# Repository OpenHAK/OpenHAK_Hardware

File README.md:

# OpenHAK Hardware
## OpenSource Health Activity Kit Hardware Files

KiCad files for the beta OpenHAK boards. 

**Check the branches tab! There is a branch for the BioHacking Village Badge at DEFCON 27 and also a OSH Park Beta Tester branch**

### WARNING: Siblees don't exist!

Hi. Here you'll find everything that you need to make yourself your very own OpenHAK! If, that is, you have any spare [Simblees](https://www.digikey.com/product-detail/en/rf-digital-corporation/RFD77101/1562-1034-ND/5723430) lying around. Should you do have some Simblees that are just taking up space, then you're in luck! Simblees are very well trained to handle reflow with a hot air gun or toaster oven many, many times. Trust me, they are tough buggers. If you *don't* have any Simblees propping open your window or shimming up your wobbly cafe table, then you're out of luck... Or are you....?

## What's going on?

**O**pen**HAK** is an **O**pen source **H**ealth **A**ctivity **K**it. Right out of the box you can wear it on your wrist (or your ankle, if you're into that kind of thing) and start tracking your steps and heart rate with a mobile app. No kidding. All of it is open-source and ready to use, modify, and share. We *were* going to call it an **O**pen **S**ource **H**ealth **I**nformation **T**racker, but we don't want to confuse people.

## Who owns the data?

Data? What data? We don't own anything. We don't keep secrets from you, or try to distract you with shiny things while we stuff your data into our AI mattress monster. No. All the data is yours. YOU can delete it or share it or analyze it or whatever it. We don't care, just don't ask us for it 'cause we don't have it. It's yours and it gets stored on your phone, or tablet, or whatever you hack the OpenHAK to spit your data into.

## What's in the box

So glad you asked. Right now, we are engaging with our beta testers and the hardware has some features that we are excitedly happy to tell you about.

* BLE
	* Yes, it's a Simblee, but it's still a pretty awesome BTLE module that can do some incredibly cool stuff. We are supporting our very own OpenHAK Arduino board variant that is based on the the original Simblee board files. We've made it easy to create the .zip packet you need to upload new code over-the-air. Every OpenHAK comes preprogrammed with Nordic's DFU library installed, so you can write your own firmware and upload it over the air from your phone to your OpenHAK.
* BMI160
	* This multi-axis MEMS monster is what we're using to count your steps, and interface with your finger tapy tap taps. We are revealing full access to it's inner guts for you to transmogrify the OpenHAK into a gesture controller so you can control your monster robot to slay your adversary's monster robot(s) with a simple gesture.
* MAX30101
	* Yes, it's a MAX integrated heart rate sensor. In the BETA version we are using the MAX3010**1** variant. If you've ever used them they are super fun to play with. **We know.** It's not easy to get heart rate off of the wrist/ankle. It's not impossible, but it's hard. That's part of the reason why we're doing this, to see how an open-source community can come together and find creative ways to solve this among many problems.
* ACCESSORIES
	* We are breaking out a handful of pins (8 for the BETA version, 10 for the BioHacking Village Badge) that are user accessible. These are useful as an Arduino compatible program interface. Also, um, maybe driving an OLED display? To, maybe, let you know when your friend is texting you ('cause it's connected to your phone...)? It could also drive an ERM (vibrator, ahem) to provide haptic feedback about stuff. The point is that since it's open-source, it's up to you. We will put up PCB design guidelines and templates so that you can create the thing you want to wear on your wrist/ankle/ahem.

## What else

The board is fit with physical features that will capture pins from an 18mm watch band. 18mm is a standard watch band size so you can accessorize with watch bands to your heart's delight!

## And
We placed the MAX30101 sensor all by itself on the (recommended) skin side of the board. We did this to facilitate enclosure design. We have a prototype case (link) that performs well under reasonable circumstances (no, we haven't mountain-biked in a wintery mix with it yet...).

If you've gotten this far then you're not even halfway down! Keep mining this repo and, don't be shy, we're only an issue away!

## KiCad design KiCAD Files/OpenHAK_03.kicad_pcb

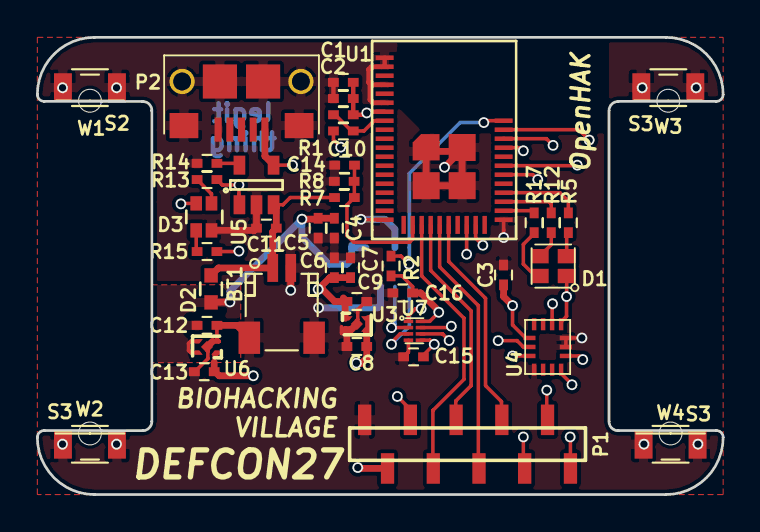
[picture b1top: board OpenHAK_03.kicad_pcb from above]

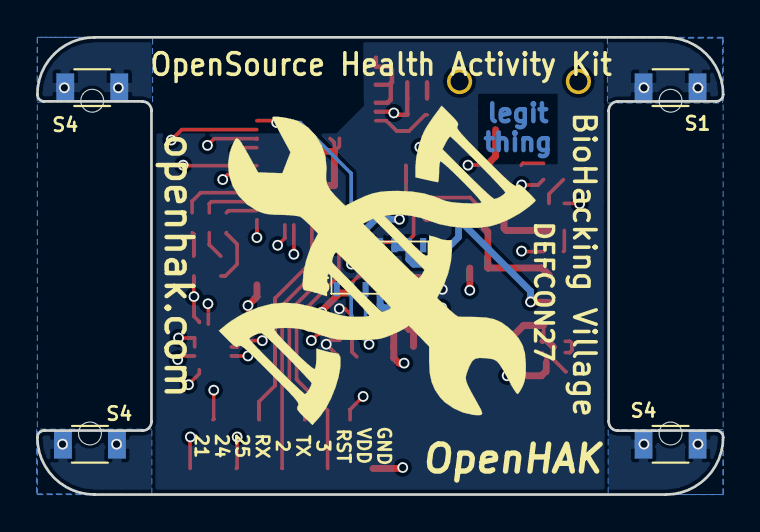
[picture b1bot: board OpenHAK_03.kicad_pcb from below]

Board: 4 copper layers, 38.1 x 25.4 mm, 51 parts (5 on the bottom side), 33 nets.

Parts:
BT1: Battery; JST_SH_SM02B-SRSS-TB_02x1.00mm_Angled
C1, C7, C10, C15, C16: 0.1uF; C_0402
C2, C4, C6, C8, C9, C12, C13, C14: 1uF; C_0402
C3, C5, C11: 10uF; C_0402
D1: ASMB-KTF0-0A306; CLMVB-FKA-CFHEHLCBB7a363
D2: D_Schottky; C_0603
D3: 18-225SURSYGC/S530-A4/E4/TR8; 0606_Bi-Color
P1: Harwin M52 Series; M52-Series_Harwin_SMT_10P
P2: USB_OTG; 10118193_microUSB
R1, R14: 10K; C_0402
R2: 4K7; C_0402
R5, R12, R17: 100R; C_0402
R7, R8: 1M; C_0402
R13, R15: 470; C_0402
S1, S2, S3, S3#2, S3#3, S4, S4#2, S4#3: C_1206
U1: rfd_77101; RFD77101
U2: MAX30100
U3: MIC5365-1.8YMT-TZ; MLF-4 1mm x 1mm
U4: BMI160; LGA_2.5x3
U5: MCP73831T-2ATI/OT; SOT-23-5
U6: MIC5365-3.0YMT-TZ; MLF-4 1mm x 1mm
U7: TXS0102DQER; X2SON8_1.4mm_x_1mm
W1, W2, W3, W4: Watch_Pin_50mil

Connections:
+1V8: C6.1, C7.2, C9.2, C15.2, U2.11, U3.1, U7.1, U7.5
/1V8_SCL: U2.2, U7.3
/1V8_SDA: U2.3, U7.2
/3V3_SCL: U1.28, U4.13, U7.6
/3V3_SDA: U1.27, U4.14, U7.7
/BMI_INT1: U1.40, U4.4
/BMI_INT2: U1.39, U4.9
/B_LED: R17.2, U1.31
/G_LED: R12.2, U1.32
/MAX_INT: R2.2, U1.41, U2.13
/PIN_2: P1.6, U1.24
/PIN_3: P1.4, U1.22
/PIN_21: P1.10, U1.36
/PIN_24: P1.9, U1.35
/PIN_25: P1.8, U1.38
/R_LED: R5.2, U1.33
/SIM_RST: C10.2, R1.2, U1.8
/SIM_RX: P1.7, U1.25
/SIM_TX: P1.5, U1.23
/V_BATT: BT1.1, C11.2, D2.2, R7.2, U5.3
/V_SENSE: C14.2, R7.1, R8.2, U1.21
GND: BT1.2, C1.1, C2.1, C3.1, C4.2, C5.2, C6.2, C7.1, C8.1, C9.1, C11.1, C12.1, C13.1, C14.1, C15.1, C16.1, D3.2, P1.1, P2.5, P2.6, P2.7, P2.8, P2.9, P2.10, P2.11, R8.1, R14.2, S1.1, S1.2, S2.1, S2.2, S3.1, S3.2, S3#2.1, S3#2.2, S3#3.1, S3#3.2, S4.1, S4.2, S4#2.1, S4#2.2, S4#3.1, S4#3.2, U1.1, U1.2, U1.4, U1.6, U1.19, U1.30, U1.42, U1.43, U1.44, U1.45, U2.4, U2.12, U3.2, U3.5, U4.1, U4.6, U4.7, U5.2, U6.2, U6.5, U7.4
unnamed: C10.1, P1.3
unnamed: D1.2, R17.1
unnamed: D1.3, R12.1
unnamed: D1.4, R5.1
unnamed: D3.1, R13.2
unnamed: D3.3, P2.1, U5.4
unnamed: D3.4, R15.2
unnamed: R13.1, R15.1, U5.1
unnamed: R14.1, U5.5
VDD: C1.2, C2.2, C3.2, C8.2, C13.2, C16.2, D1.1, P1.2, R1.1, R2.1, U1.7, U3.3, U3.4, U4.5, U4.8, U4.12, U6.1, U7.8
VPP: C4.1, C5.1, C12.2, D2.1, U2.9, U2.10, U6.3, U6.4

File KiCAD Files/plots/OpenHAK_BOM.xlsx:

Id | Designator | Package | Quantity | Designation | Manufacturer | Part Number | Distributor | Alternate Part Number | Notes
1 | BT1 | JST_SH_SM02B-SRSS-TB_02x1.00mm_Angled | 1 | Battery | JST | SM02B-SRSS-TB(LF)(SN) | TLC |  | https://www.tlcelectronics.com/tlc-3892.html
2 | C1,C7,C10,C14,C15,C16 | C_0402 | 6 | 0.1uF | Yaego | CC0402KRX5R6BB104 | Mouser
3 | C2,C4,C6,C8,C9,C12,C13 | C_0402 | 7 | 1uF | Taiyo | JMK105C6105MV-F | Mouser
4 | C3,C5,C11 | C_0402 | 3 | 10uF | Murata | GRM155R60G106ME44J | Mouser
5 | D1 | CLMVB-FKA-CFHEHLCBB7a363 | 1 | Led_RGB_CA | Broadcom | ASMB-KTF0-0A306 | Mouser | CLMVB-FKA-CFHEHLCBB7A363
6 | D2 | C_0603 | 1 | D_Schottky | Comchip | CDBU0130L | Mouser
7 | D3 | 0606_Bi-Color | 1 | Dialight_R_G_LED | Everlight | 18-225SURSYGC/S530-A4/E4/TR8 | Mouser
8 | P1 | 1x10_SMT_F | 1 | CONN_01X10 | Harwin | M52-5051045 | Newark |  | Mates with M52-040023V1045 to provide 8.5mm stack
9 | P2 | 10118193_microUSB | 1 | USB_OTG | Amphenol | 10118193-0001LF | Vertical
10 | R1,R2,R14 | C_0402 | 3 | 10K | Vishay | CRCW040210K0JNEDC | Mouser
11 | R13,R15 | C_0402 | 2 | 470R | Yaego | RC0402JR-13470RL | Mouser
12 | R5,R12,R17 | C_0402 | 3 | 100R | Yaego | RC0402FR-07100RL | Mouser
13 | R7,R8 | C_0402 | 2 | 1M | Yaego | RC0402FR-071ML | Mouser
14 | S3,S4,S4,S3,S3,S4,S1,S2 | C_1206 | 8 | Watch Pin | Vishay | CRCW12060000Z0EBC | Mouser
15 | U1 | RFD77101 | 1 | rfd_77101 | RFDigital | RFD77101 | xxx
16 | U2 | MAX3010x | 1 | MAX301_Series | Maxim | MAX30101EFD+ | Mouser
17 | U3 | MLF-4 1mm x 1mm | 1 | MIC5365 | Microchip | MIC5365-1.8YMT-TZ | Mouser
18 | U6 | MLF-4 1mm x 1mm | 1 | MIC5365 | Microchip | MIC5365-3.0YMT-TZ | Mouser
19 | U4 | LGA_2.5x3 | 1 | BMI160 | Bosch | BMI160 | Future Electronics
20 | U5 | SOT-23-5 | 1 | MCP73831 | Microchip | MCP73831T-2ATI/OT | Mouser
21 | U7 | X2SON8_1.4mm_x_1mm | 1 | TXS0102_LEVEL_SHIFTER_X2SON8 | Texas Instruments | TXS0102DQER | Texas Instruments

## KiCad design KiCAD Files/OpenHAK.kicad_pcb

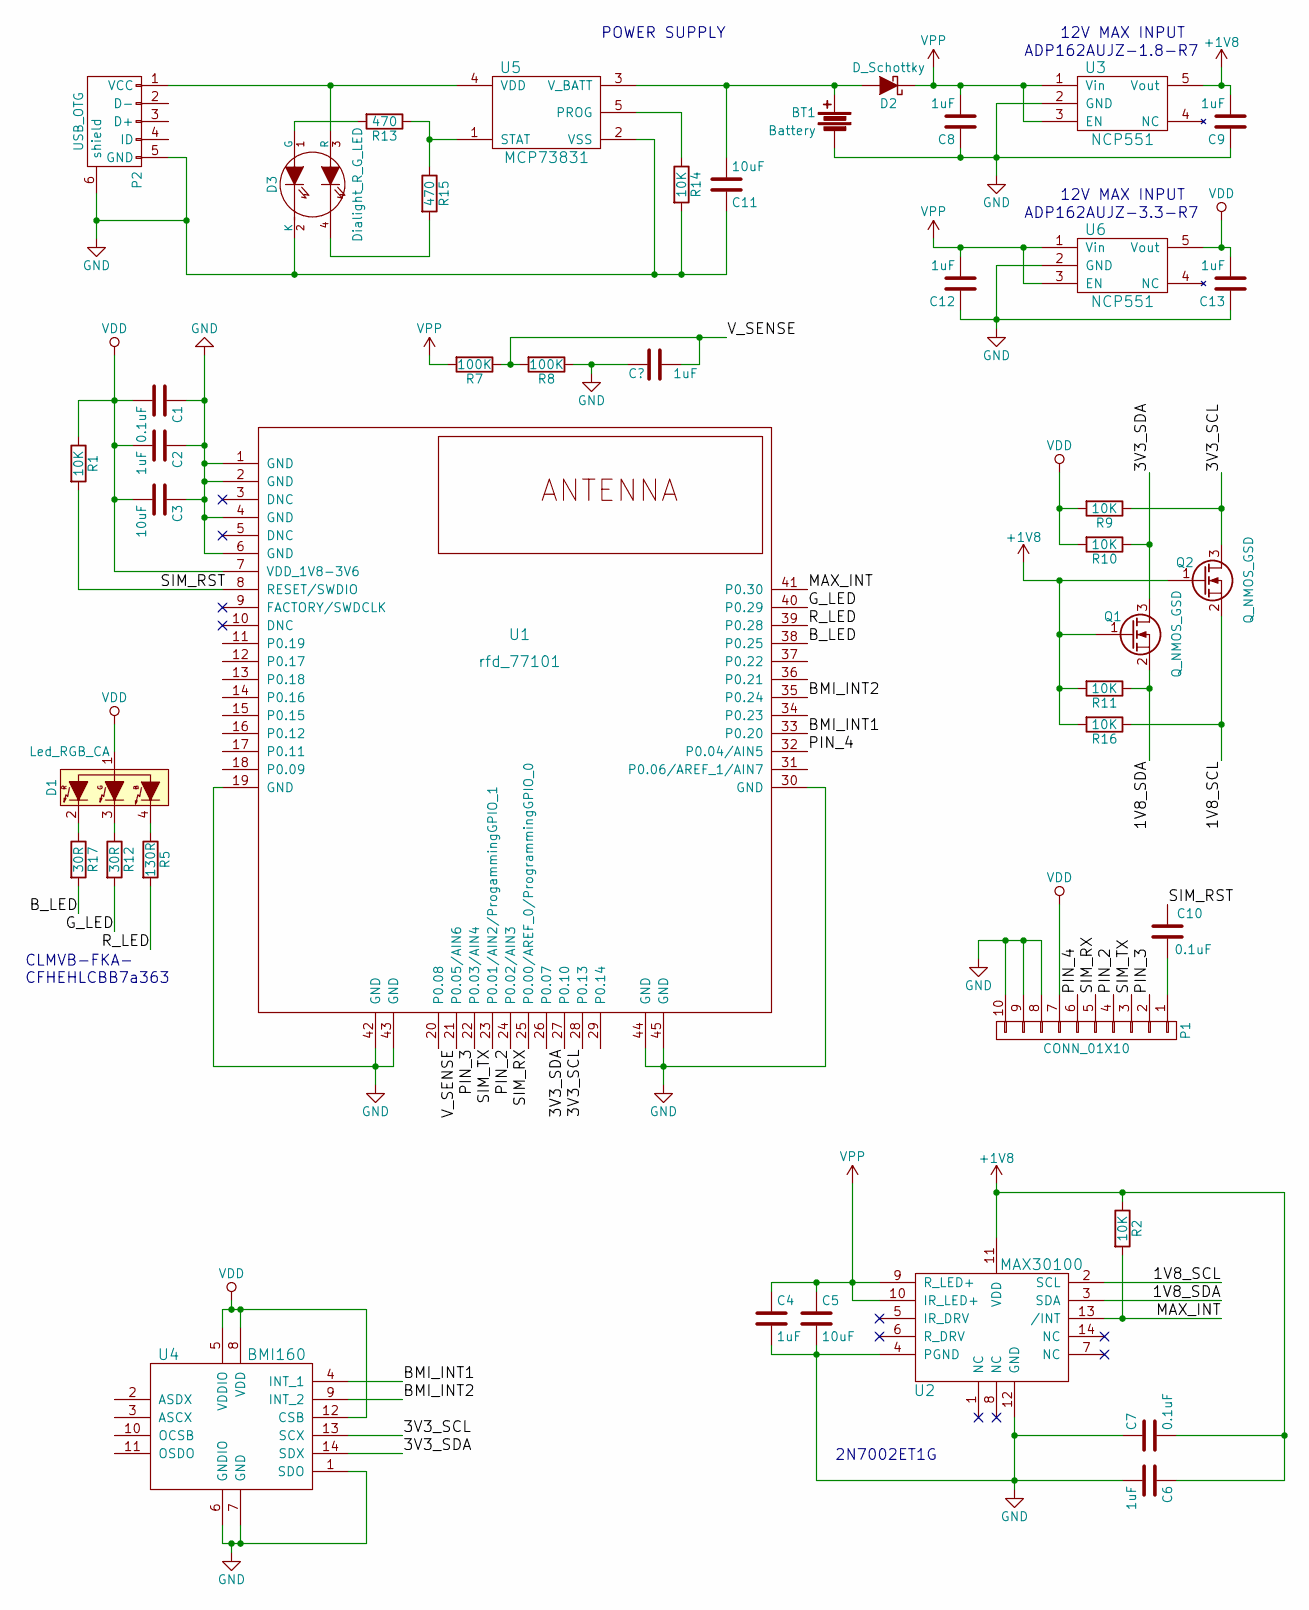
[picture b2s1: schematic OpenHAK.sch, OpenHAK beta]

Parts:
BT1: Battery; JST_RA_SMT
C1, C7, C10: 0.1uF; C_0603
C2, C4, C6, C8, C9, C12, C13: 1uF; C_0603
C3, C5, C11: 10uF; C_0603
D1: Led_RGB_CA; CLMVB-FKA-CFHEHLCBB7a363
D2: D_Schottky; C_0603
D3: Dialight_R_G_LED; 0606_Bi-Color
P1: CONN_01X10; 4u-0201GDVE06
P2: USB_OTG; 10118193_microUSB
Q1, Q2: Q_NMOS_GSD; SOT-23
R1, R2, R9, R10, R11, R14, R16: 10K; C_0603
R5: 130R; C_0603
R7, R8: 100K; C_0603
R12, R17: 30R; C_0603
R13, R15: 470; C_0603
U1: rfd_77101; RFD77101
U2: MAX30100
U3, U6: NCP551; SOT-23-5
U4: BMI160; LGA_2.5x3
U5: MCP73831; SOT-23-5

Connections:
+1V8: C6.1, C7.2, C9.2, Q1.1 (G), Q2.1 (G), R2.1, R11.2, R16.2, U2.11 (VDD), U3.5 (Vout); also elsewhere on the board
/1V8_SCL: Q2.2 (S), R16.1, U2.2 (SCL)
/1V8_SDA: Q1.2 (S), R11.1, U2.3 (SDA); also elsewhere on the board
/3V3_SCL: Q2.3 (D), R9.1, U1.28 (P0.13), U4.13 (SCX)
/3V3_SDA: Q1.3 (D), R10.1, U1.27 (P0.10), U4.14 (SDX); also elsewhere on the board
/BMI_INT1: U1.33 (P0.20), U4.4 (INT_1)
/BMI_INT2: U1.35 (P0.24), U4.9 (INT_2)
/B_LED: R17.2, U1.38 (P0.25)
/G_LED: R12.2, U1.40 (P0.29)
/MAX_INT: R2.2, U1.41 (P0.30), U2.13 (/INT)
/PIN_2: P1.4, U1.24 (P0.02/AIN3)
/PIN_3: P1.2, U1.22 (P0.03/AIN4)
/PIN_4: P1.6, U1.32 (P0.04/AIN5)
/R_LED: R5.2, U1.39 (P0.28)
/SIM_RST: C10.1, R1.2, U1.8 (RESET/SWDIO)
/SIM_RX: P1.5, U1.25 (P0.00/AREF_0/ProgrammingGPIO_0)
/SIM_TX: P1.3, U1.23 (P0.01/AIN2/ProgammingGPIO_1)
/V_SENSE: R7.1, R8.2, U1.21 (P0.05/AIN6)
GND: BT1.2, BT1.3, BT1.4, C1.1, C2.1, C3.1, C4.2, C5.2, C6.2, C7.1, C8.1, C9.1, C11.1, C12.1, C13.1, D3.2 (K), P1.8, P1.9, P1.10, P2.5 (GND), P2.6 (shield), P2.7, P2.8, P2.9, P2.10, P2.11, R8.1, R14.2, U1.1 (GND), U1.2 (GND), U1.4 (GND), U1.6 (GND), U1.19 (GND), U1.30 (GND), U1.42 (GND), U1.43 (GND), U1.44 (GND), U1.45 (GND), U2.4 (PGND), U2.12 (GND), U3.2 (GND), U4.1 (SDO), U4.6 (GNDIO), U4.7 (GND), U5.2 (VSS), U6.2 (GND)
unnamed: BT1.1, C11.2, D2.2 (A), U5.3 (V_BATT)
unnamed: C10.2, P1.1
unnamed: D1.2 (R), R17.1
unnamed: D1.3 (G), R12.1
unnamed: D1.4 (B), R5.1
unnamed: D3.1 (G), R13.2
unnamed: D3.3 (R), P2.1 (VCC), U5.4 (VDD)
unnamed: D3.4, R15.2
unnamed: R13.1, R15.1, U5.1 (STAT)
unnamed: R14.1, U5.5 (PROG)
VDD: C1.2, C2.2, C3.2, C13.2, D1.1, P1.7, R1.1, R9.2, R10.2, U1.7 (VDD_1V8-3V6), U4.5 (VDDIO), U4.8 (VDD), U4.12 (CSB), U6.5 (Vout)
VPP: C4.1, C5.1, C8.2, C12.2, D2.1 (K), R7.2, U2.9 (R_LED+), U2.10 (IR_LED+), U3.1 (Vin), U3.3 (EN), U6.1 (Vin), U6.3 (EN)

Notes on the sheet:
ADP162AUJZ-1.8-R7
POWER SUPPLY
12V MAX INPUT
2N7002ET1G
ADP162AUJZ-3.3-R7
CLMVB-FKA- CFHEHLCBB7a363

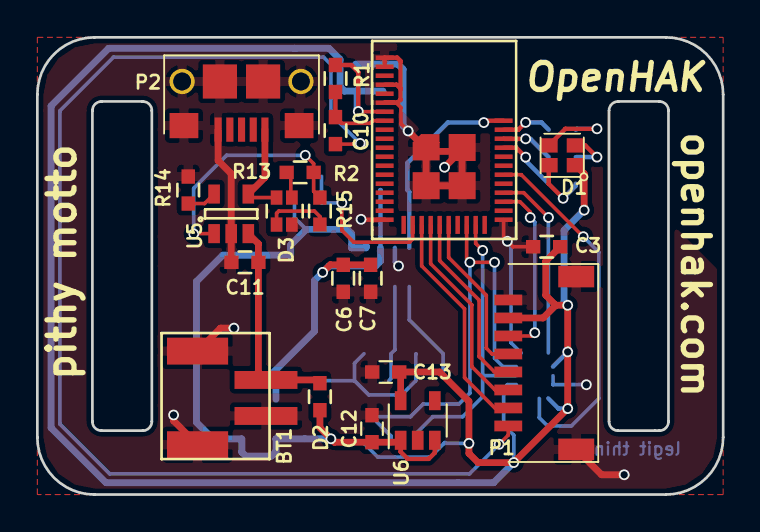
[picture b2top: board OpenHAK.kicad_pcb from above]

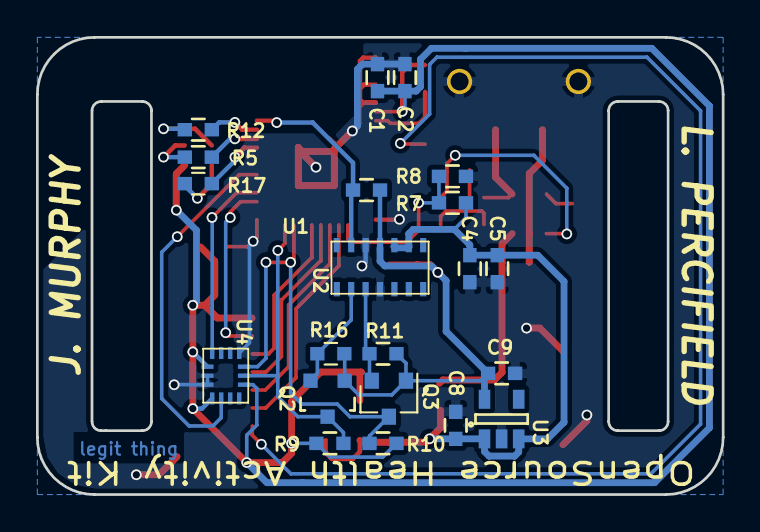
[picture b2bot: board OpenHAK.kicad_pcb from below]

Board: 2 copper layers, 38.1 x 25.4 mm, 41 parts (21 on the bottom side), 31 nets.

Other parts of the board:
Q3: Q_NMOS_GSD; SOT-23

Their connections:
+1V8: Q3.1; also elsewhere on the board
/1V8_SDA: Q3.2; also elsewhere on the board
/3V3_SDA: Q3.3; also elsewhere on the board

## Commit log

2018-02-01 Initial commit of OpenHAK beta design files
    Moving into v1 design of the OpenHAK hardware
2018-02-01 gitignore
2018-02-28 Added cap to VSENS to fix battery reading
2019-05-31 Updated with latest files
2019-06-01 edit
2019-06-15 removed some stuff we don't need and made notes about changes to pcb
2019-06-16 Major changes to the board layout
    took some things off, put some things on, and moved some things around
2019-06-16 Cleaned up silk
2019-06-17 added to ignore
2019-06-17 generated gerbers and polished bom
2019-06-17 minor things
2019-06-18 Added PDFs of the top and bottom
2019-06-19 update gitignore
2019-06-21 adjusted pad to mask clearance for DFM
2019-07-15 updated gerbers
2020-09-15 Create fp-info-cache
